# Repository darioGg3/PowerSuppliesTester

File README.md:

# PowerSuppliesTester

### Board with many outputs to test diferent DC-DC Switching power supplies

PCB designed on KiCAD 7.0

### Specifications:
  - 5 independent outputs: -12V, +12V, 3.3V, 1.8V, and PD output
  - Inputs: USB PD, Barrel up to 9V and wired input up to 9V. 

 <br>
<p>

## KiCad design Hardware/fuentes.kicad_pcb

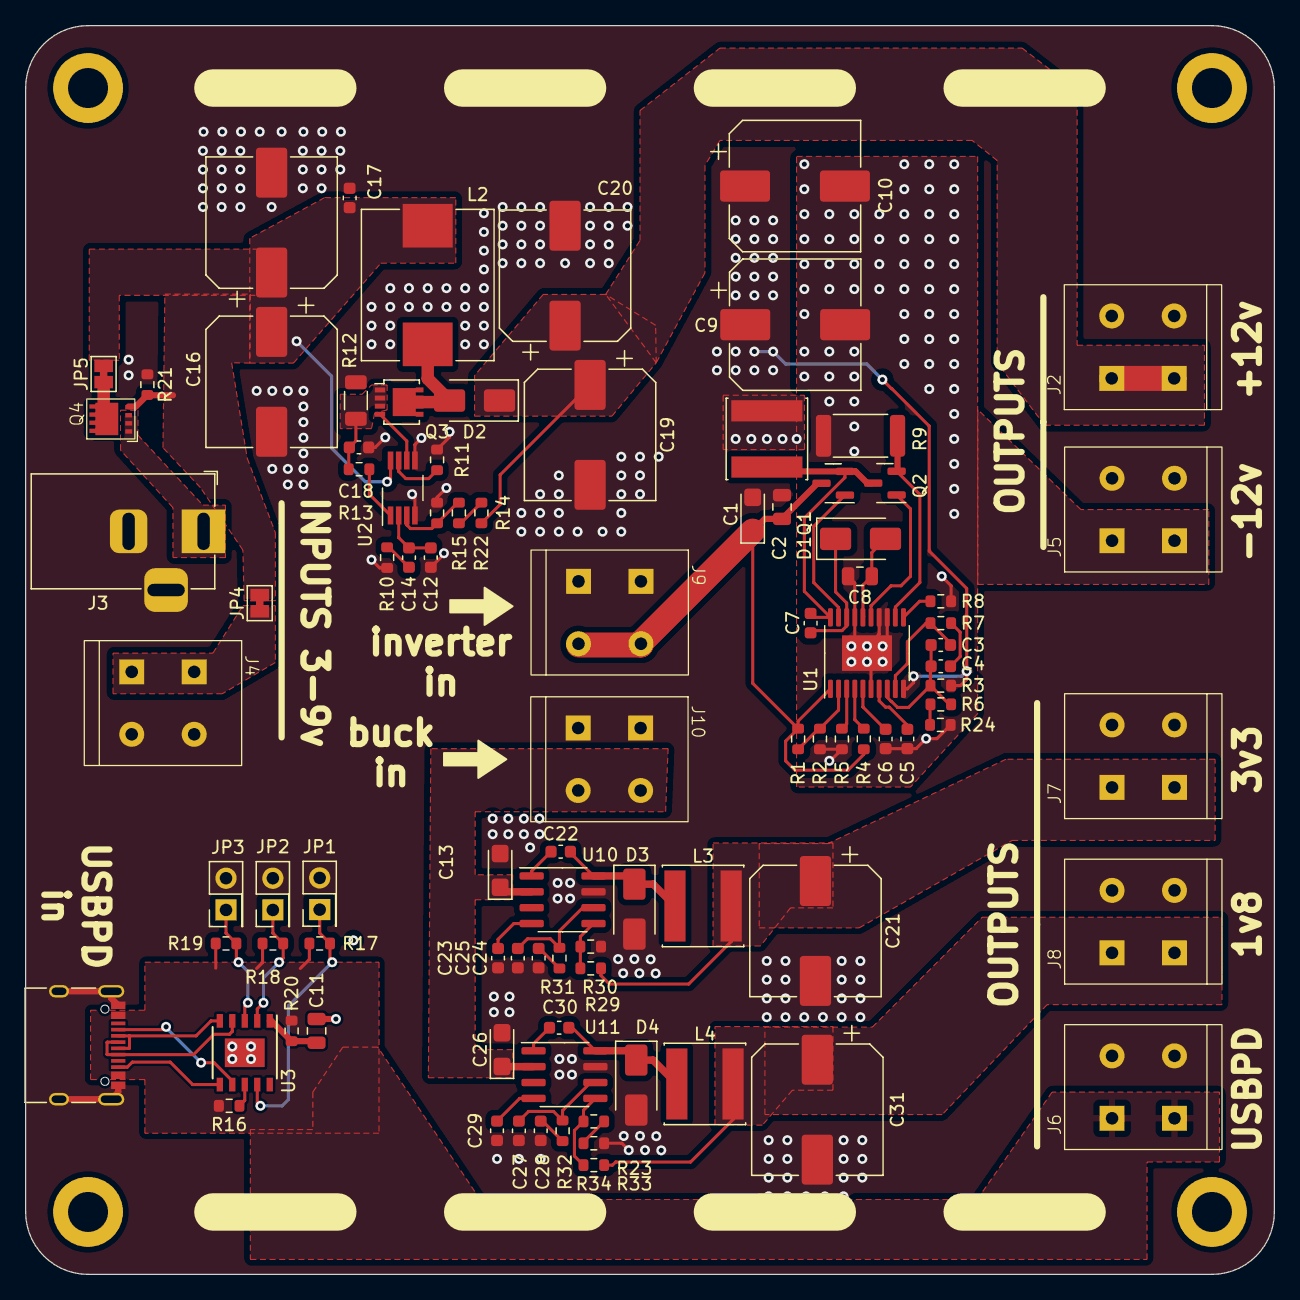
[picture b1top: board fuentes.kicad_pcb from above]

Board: 2 copper layers, 100.0 x 100.0 mm, 93 parts (0 on the bottom side), 59 nets.

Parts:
C1, C13, C26: 10u; CP_EIA-3216-18_Kemet-A
C2, C8, C11: 1u; C_0805_2012Metric
C3: 12p; C_0603_1608Metric
C4: 30p; C_0603_1608Metric
C5: 10n; C_0603_1608Metric
C6: 330p; C_0603_1608Metric
C7, C14: 100n; C_0603_1608Metric
C9, C10, C21, C31: 220u; CP_Elec_10x10
C12: 4.7nF; C_0603_1608Metric
C15, C16, C19, C20: 220uF; CP_Elec_10x10
C17, C22, C30: 100nF; C_0603_1608Metric
C18: 47pF; C_0603_1608Metric
C23, C29: 10nF; C_0603_1608Metric
C24, C28: 1nF; C_0603_1608Metric
C25, C27: 10pF; C_0603_1608Metric
D1, D3, D4: SS54; D_SMA
D2: ss54; D_SMA
J1: USB_C_Receptacle_USB2.0; USB_C_Receptacle_XKB_U262-16XN-4BVC11
J2, J4, J5, J6, J7, J8, J9, J10: C784939; XY119A-5.0-2P
J3: Barrel_Jack; BarrelJack_Horizontal
JP1, JP2, JP3: JP_O; PinHeader_2x01_P2.54mm_Vertical
JP4, JP5: Jumper_Bridged; SolderJumper-2_P1.3mm_Bridged_Pad1.0x1.5mm
L1, L3, L4: C83454; L_Sunlord_SWPA6045S
L2: C167228; L_Chilisin_BMRF00101040
Q1, Q2: AO3480C; SOT-23
Q3: NTTFS4C25NTWG; LFPAK33
Q4: AP30P30Q
R1: 8.2k; R_0603_1608Metric
R2: 1k; R_0603_1608Metric
R3: 24k; R_0603_1608Metric
R4: 1M; R_0603_1608Metric
R5: 3k; R_0603_1608Metric
R6, R34: 1.5k; R_0603_1608Metric
R7: 510k; R_0603_1608Metric
R8, R16, R17, R18, R19, R20, R22: 10k; R_0603_1608Metric
R9: C620826; R_2512_6332Metric
R10, R24: 1.2k; R_0603_1608Metric
R11: 2.2k; R_0603_1608Metric
R12: 4mOhm; R_1206_3216Metric
R13, R21, R23: 100; R_0603_1608Metric
R14: 100k; R_0603_1608Metric
R15: 13k; R_0603_1608Metric
R29: 7.5k; R_0603_1608Metric
R30: 2.4k; R_0603_1608Metric
R31, R32: 22k; R_0603_1608Metric
R33: 2k; R_0603_1608Metric
U1: LM5116; HTSSOP-20-1EP_4.4x6.5mm_P0.65mm_EP2.85x4mm
U2: LM3488; VSSOP-8_3.0x3.0mm_P0.65mm
U3: CH224K; SSOP-10_3.9x4.9mm_P1.00mm
U10, U11: TPS54331; SOIC-8_3.9x4.9mm_P1.27mm

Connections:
+1V8: C31.1, J8.1, L4.2, R33.1
+3V3: C21.1, J7.1, L3.2, R29.1
+12V: C19.1, C20.1, D2.1 (K), J2.1, R22.2
-12V: C5.2, C6.2, C8.2, C9.2, C10.2, J5.1, R2.2, R5.2, R8.2, R9.2, R24.2, U1.6 (AGND), U1.13 (CSG), U1.14 (PGND), U1.17 (VCCX), U1.21 (PGND)
/BOOST/Isense: C18.1, Q3.1 (S), Q3.2 (S), Q3.3 (S), R12.1, R13.2
/USB_PD/CC1: J1.A5 (CC1), U3.7 (CC1)
/USB_PD/CC2: J1.B5 (CC2), U3.6 (CC2)
/USB_PD/DM: J1.A7 (D-), J1.B7 (D-), U3.5 (DM)
/USB_PD/DP: J1.A6 (D+), J1.B6 (D+), U3.4 (DP)
GND: C1.2, C2.2, C9.1, C10.1, C11.2, C12.2, C13.2, C15.2, C16.2, C17.2, C18.2, C19.2, C20.2, C21.2, C23.2, C24.2, C25.2, C26.2, C27.2, C28.2, C29.2, C31.2, D3.2 (A), D4.2 (A), J1.A1 (GND), J1.B1 (GND), J1.S1 (SHIELD), J2.2, J3.2, J3.3, J4.2, J5.2, J6.2, J7.2, J8.2, J9.1, J10.1, JP1.2 (B), JP2.2 (B), JP3.2 (B), L1.2, R3.1, R10.2, R11.2, R12.2, R15.2, R21.1, R23.2, R30.2, U1.10 (VOUT), U2.4 (AGND), U2.5 (PGND), U3.0 (GND), U10.7 (GND), U11.7 (GND)
unnamed: C4.1, R7.2
unnamed: C14.2, R10.1
unnamed: C24.1, R31.2
unnamed: C28.1, R32.2
unnamed: C8.1, D1.2 (A), U1.16 (VCC)
unnamed: C7.1, D1.1 (K), U1.18 (HB)
unnamed: D2.2 (A), L2.2, Q3.5 (D)
unnamed: C22.2, D3.1 (K), L3.1, U10.8 (PH)
unnamed: C30.2, D4.1 (K), L4.1, U11.8 (PH)
unnamed: JP1.1 (A), R17.2, U3.9 (CFG1)
unnamed: JP2.1 (A), R18.2, U3.2 (CFG2)
unnamed: JP3.1 (A), R19.2, U3.3 (CFG3)
unnamed: JP5.1 (A), Q4.5
unnamed: Q1.1 (G), U1.19 (HO)
unnamed: C7.2, L1.1, Q1.2 (S), Q2.3 (D), U1.20 (SW)
unnamed: Q2.1 (G), U1.15 (LO)
unnamed: Q2.2 (S), R9.1, U1.12 (CS)
unnamed: Q3.4 (G), U2.6 (DR)
unnamed: R14.2, R22.1
unnamed: R23.1, R34.2
unnamed: R6.2, R24.1
unnamed: C3.1, R7.1, U1.9 (COMP)
unnamed: R8.1, U1.11 (DEMB)
unnamed: R4.2, U1.4 (EN)
unnamed: C3.2, C4.2, R3.2, R6.1, U1.8 (FB)
unnamed: C6.1, U1.5 (RAMP)
unnamed: R5.1, U1.3 (RT/SYNC)
unnamed: C5.1, U1.7 (SS)
unnamed: R1.2, R2.1, U1.2 (UVLO)
unnamed: C12.1, C14.1, U2.2 (COMP)
unnamed: R11.1, U2.7 (FA/SD)
unnamed: R14.1, R15.1, U2.3 (FB)
unnamed: R13.1, U2.1 (I_{SEN})
unnamed: R16.2, U3.8 (VBUS)
unnamed: C11.1, R20.2, U3.1 (VDD)
unnamed: C22.1, U10.1 (BOOT)
unnamed: C25.1, R31.1, U10.6 (COMP)
unnamed: C23.1, U10.4 (SS)
unnamed: R29.2, R30.1, U10.5 (VSENSE)
unnamed: C30.1, U11.1 (BOOT)
unnamed: C27.1, R32.1, U11.6 (COMP)
unnamed: C29.1, U11.4 (SS)
unnamed: R33.2, R34.1, U11.5 (VSENSE)
V9-12: C1.1, C2.1, J9.2, Q1.3 (D), R1.1, R4.1, U1.1 (VIN)
V9-12_B: C13.1, C26.1, J10.2, U10.2 (VIN), U11.2 (VIN)
VBARREL: J3.1, Q4.1, Q4.2 (S), Q4.3 (S)
VBoostIn: C15.1, C16.1, C17.1, JP4.2 (B), JP5.2 (B), L2.1, Q4.4, R21.2, U2.8 (V_{IN})
VDC1: J4.1, JP4.1 (A)
VUSB1: J1.B4 (VBUS), J1.B9 (VBUS), J6.1, R16.1, R17.1, R18.1, R19.1, R20.1

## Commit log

2024-01-15 readme and photo added
2024-01-15 update photo
2024-01-15 edit photo
2024-01-23 change some name files
2024-01-23 edit readme
